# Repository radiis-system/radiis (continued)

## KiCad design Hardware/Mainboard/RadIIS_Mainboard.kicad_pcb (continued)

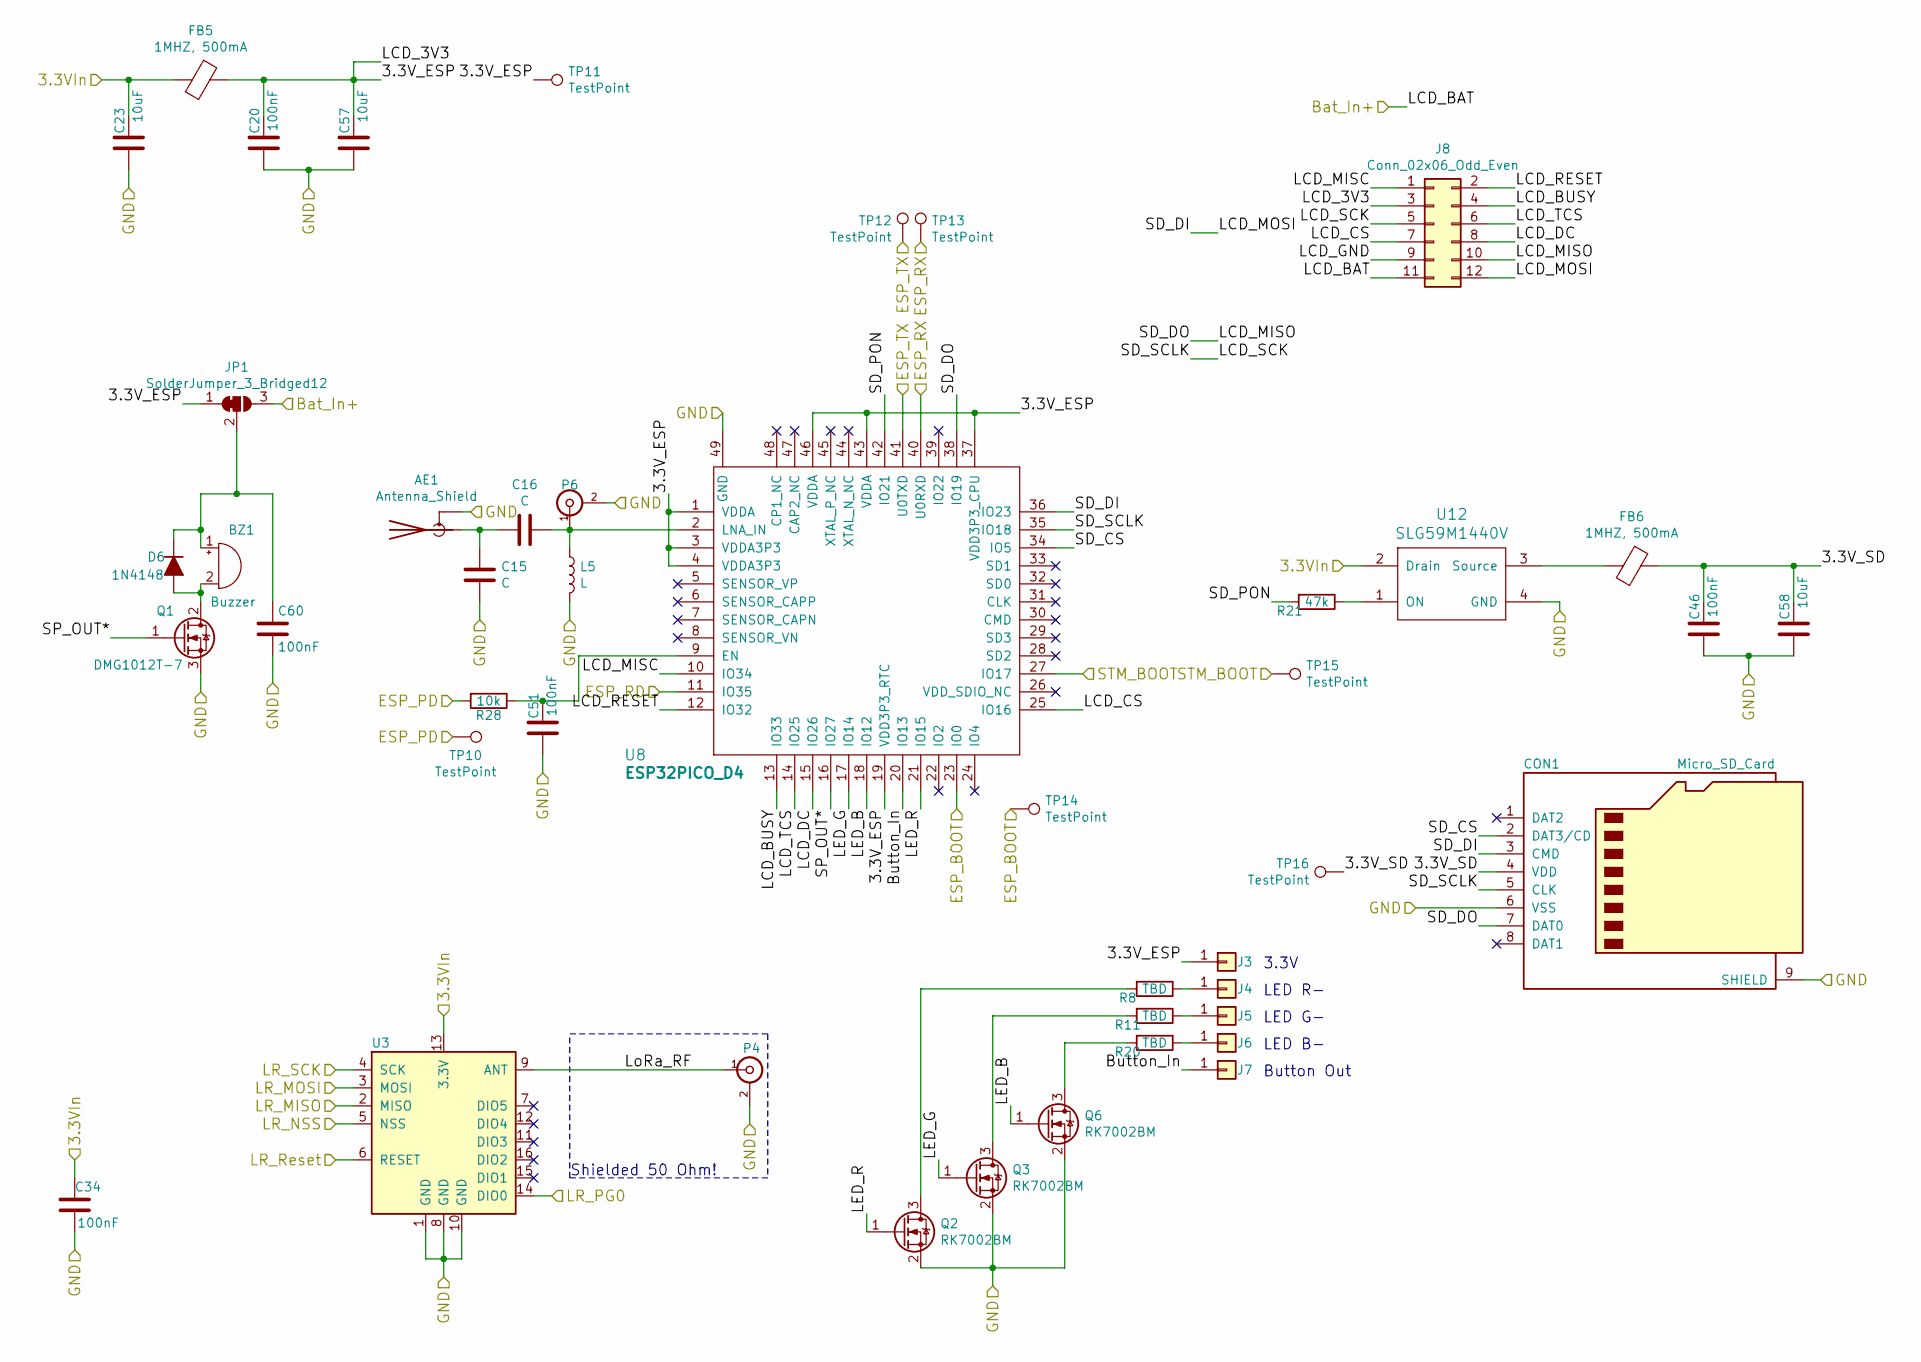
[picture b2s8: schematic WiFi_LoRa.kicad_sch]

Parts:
AE1: Antenna_Shield; Proant440; Digikey Nr 1532-1001-1-ND
BZ1: Buzzer; CUI_CMT-5023S-SMT; Digikey Nr 102-3743-1-ND
C15, C16: C; C_0402_1005Metric; Digikey Nr TBD (HF)
C20, C34, C46, C51, C60: 100nF; C_0603_1608Metric; Digikey Nr 1276-1000-1-ND
C23, C57, C58: 10uF; C_0603_1608Metric; Digikey Nr 478-10766-1-ND
CON1: Micro_SD_Card; microSD_HC_Wuerth_693072010801; Digikey Nr 732-3820-1-ND
D6: 1N4148; D_SOD-523; Digikey Nr 1N4148XTPMSCT-ND
FB5, FB6: 1MHZ, 500mA; L_0603_1608Metric; Digikey Nr 445-2205-1-ND
J3, J4, J5, J6, J7: Conn_01x01; 2108693-4; Digikey Nr A118885CT-ND
J8: Conn_02x06_Odd_Even; PinHeader_2x06_P1.27mm_Vertical_SMD; Digikey Nr S9012E-06-ND
JP1: SolderJumper_3_Bridged12; SolderJumper-3_P1.3mm_Bridged12_RoundedPad1.0x1.5mm; Digikey Nr NA
L5: L; L_0402_1005Metric; Digikey Nr TBD (HF)
P4, P6: A-1JB (U.FL); U.FL_SMD_Amp; Digikey Nr ARF1579CT-ND
Q1: DMG1012T-7; TSOT-23; Digikey Nr DMG1012T-7DICT-ND
Q2, Q3, Q6: RK7002BM; SOT-23; Digikey Nr RK7002BMT116CT-ND
R8, R11, R20: TBD; R_0603_1608Metric; Digikey Nr TBD
R21: 47k; R_0603_1608Metric; Digikey Nr 311-47.0KHRCT-ND
R28: 10k; R_0603_1608Metric; Digikey Nr 311-10.0KHRCT-ND
TP10, TP11, TP12, TP13, TP14, TP15, TP16: TestPoint; TestPoint_Pad_D1.5mm
U3: RFM95W-868S2; HOPERF_RFM9XW_SMD
U8: ESP32PICO_D4; QFN-48-1EP_7x7mm_Pitch0.5mm; Digikey Nr 1904-1029-1-ND
U12: SLG59M1440V; STDFN-4; Digikey Nr 1827-1058-1-ND

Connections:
+3V3: C23.2, C34.2, FB5.2, U3.13 (3.3V), U12.2 (Drain); also elsewhere on the board
+BATT: J8.11, JP1.3 (B); also elsewhere on the board
/Nucleo/STM_BOOT: TP15.1, U8.27 (IO17); also elsewhere on the board
/WiFi_LoRa/3.3V_ESP: C20.2, C57.2, FB5.1, J3.1, J8.3, JP1.1 (A), TP11.1, U8.1 (VDDA), U8.3 (VDDA3P3), U8.4 (VDDA3P3), U8.19 (VDD3P3_RTC), U8.37 (VDD3P3_CPU), U8.43 (VDDA), U8.46 (VDDA)
/WiFi_LoRa/3.3V_SD: C46.2, C58.2, CON1.4 (VDD), FB6.1, TP16.1
/WiFi_LoRa/Button_In: J7.1, U8.20 (IO13)
/WiFi_LoRa/ESP_BOOT: TP14.1, U8.23 (IO0); also elsewhere on the board
/WiFi_LoRa/ESP_PD: R28.2, TP10.1; also elsewhere on the board
/WiFi_LoRa/ESP_RD: U8.11 (IO35); also elsewhere on the board
/WiFi_LoRa/ESP_RX: TP13.1, U8.40 (U0RXD); also elsewhere on the board
/WiFi_LoRa/ESP_TX: TP12.1, U8.41 (U0TXD); also elsewhere on the board
/WiFi_LoRa/LCD_BUSY: J8.4, U8.13 (IO33)
/WiFi_LoRa/LCD_CS: J8.7, U8.25 (IO16)
/WiFi_LoRa/LCD_DC: J8.8, U8.15 (IO26)
/WiFi_LoRa/LCD_GND: J8.9
/WiFi_LoRa/LCD_MISC: J8.1, U8.10 (IO34)
/WiFi_LoRa/LCD_MISO: CON1.7 (DAT0), J8.10, U8.38 (IO19)
/WiFi_LoRa/LCD_MOSI: CON1.3 (CMD), J8.12, U8.36 (IO23)
/WiFi_LoRa/LCD_RESET: J8.2, U8.12 (IO32)
/WiFi_LoRa/LCD_SCK: CON1.5 (CLK), J8.5, U8.35 (IO18)
/WiFi_LoRa/LCD_TCS: J8.6, U8.14 (IO25)
/WiFi_LoRa/LED_B: Q6.1 (G), U8.18 (IO12)
/WiFi_LoRa/LED_G: Q3.1 (G), U8.17 (IO14)
/WiFi_LoRa/LED_R: Q2.1 (G), U8.21 (IO15)
/WiFi_LoRa/LR_MISO: U3.2 (MISO); also elsewhere on the board
/WiFi_LoRa/LR_MOSI: U3.3 (MOSI); also elsewhere on the board
/WiFi_LoRa/LR_NSS: U3.5 (NSS); also elsewhere on the board
/WiFi_LoRa/LR_PG0: U3.14 (DIO0); also elsewhere on the board
/WiFi_LoRa/LR_Reset: U3.6 (RESET); also elsewhere on the board
/WiFi_LoRa/LR_SCK: U3.4 (SCK); also elsewhere on the board
/WiFi_LoRa/LoRa_RF: P4.1 (In), U3.9 (ANT)
/WiFi_LoRa/SD_CS: CON1.2 (DAT3/CD), U8.34 (IO5)
/WiFi_LoRa/SD_PON: R21.2, U8.42 (IO21)
/WiFi_LoRa/SP_OUT*: Q1.1 (G), U8.16 (IO27)
GND: AE1.2 (Shield), C15.1, C20.1, C23.1, C34.1, C46.1, C51.1, C57.1, C58.1, C60.2, CON1.6 (VSS), CON1.9 (SHIELD), L5.2, P4.2 (Ext), P6.2 (Ext), Q1.3 (S), Q2.2 (S), Q3.2 (S), Q6.2 (S), U3.1 (GND), U3.8 (GND), U3.10 (GND), U8.49 (GND), U12.4 (GND); also elsewhere on the board
unnamed: AE1.1 (A), C15.2, C16.2
unnamed: BZ1.1 (-), C60.1, D6.1 (K), JP1.2 (C)
unnamed: BZ1.2 (+), D6.2 (A), Q1.2 (D)
unnamed: C16.1, L5.1, P6.1 (In), U8.2 (LNA_IN)
unnamed: C51.2, R28.1, U8.9 (EN)
unnamed: FB6.2, U12.3 (Source)
unnamed: J4.1, R8.1
unnamed: J5.1, R11.1
unnamed: J6.1, R20.1
unnamed: Q2.3 (D), R8.2
unnamed: Q3.3 (D), R11.2
unnamed: Q6.3 (D), R20.2
unnamed: R21.1, U12.1 (ON)

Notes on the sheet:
LED B-
Shielded 50 Ohm!
3.3V
Button Out
LED G-
LED R-

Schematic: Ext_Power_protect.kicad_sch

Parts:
C39: 100nF 50V; C_0603_1608Metric; Digikey Nr 1292-1392-1-ND
C40: 10uF 50V; C_1206_3216Metric; Digikey Nr 1276-6736-1-ND
C41: 22nF; C_0603_1608Metric; Digikey Nr 399-1280-1-ND
C42, C43: 22uF; C_0805_2012Metric; Digikey Nr 1276-6780-1-ND
D7: D_Schottky_ALT; D_SOD-123F; Digikey Nr MBR230LSFT1GOSCT-ND
FB2: 1MHZ, 500mA; L_0603_1608Metric; Digikey Nr 445-2205-1-ND
L2: 4.7uH; L_Taiyo-Yuden_NR-50xx; Digikey Nr 587-2407-1-ND
R31: NA/0; R_0603_1608Metric; Digikey Nr 311-0.0GRCT-ND
R32: 10k; R_0603_1608Metric; Digikey Nr 311-10.0KHRCT-ND
R33: 47k; R_0603_1608Metric; Digikey Nr 311-47.0KHRCT-ND
U13: TS30041/11; QFN-16-1EP_3x3mm_Pitch0.5mm; Digikey Nr TS30041-M000QFNRCT-ND
W20: TEST_1P; TestPoint_Pad_D1.0mm; Digikey Nr NA

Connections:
/Ext_Power_protect/EN_DCDCin: U13.9 (EN); also elsewhere on the board
/Ext_Power_protect/PG_DCDCin: U13.8 (PG); also elsewhere on the board
/Ext_Power_protect/VSW: C41.2, D7.1 (K), L2.1, U13.1 (VSW), U13.12 (VSW), U13.13 (VSW), U13.16 (VSW)
/Ext_Vin: FB2.2; also elsewhere on the board
/Reg_5V: C42.2, C43.2, L2.2, R31.1, R33.1, W20.1; also elsewhere on the board
GND: C39.1, C40.2, C42.1, C43.1, D7.2 (A), R32.1, U13.4 (GND), U13.14 (PGND), U13.15 (PGND), U13.17 (GND); also elsewhere on the board
unnamed: C39.2, C40.1, FB2.1, R31.2, U13.2 (VCC), U13.3 (VCC), U13.11 (VCC)
unnamed: C41.1, U13.10 (BST)
unnamed: R32.2, R33.2, U13.5 (FB)
unnamed: U13.6 (NC), U13.7 (NC)

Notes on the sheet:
If TS300x1 not assembled, R = 0 Ohm
max 40V
shielded

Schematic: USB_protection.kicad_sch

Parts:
C49: 680nF; C_0603_1608Metric; Digikey Nr 732-7970-1-ND
FB3, FB4: Ferrite Bead; L_0603_1608Metric; Digikey Nr 732-1593-1-ND
R35, R36: 22; R_0603_1608Metric; Digikey Nr 311-22.0HRCT-ND
U14: IP4220CZ6; SC-74; Digikey Nr 1727-3578-1-ND
W21: TEST_1P; TestPoint_Pad_D1.0mm; Digikey Nr NA

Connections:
+5VP: FB3.2, W21.1; also elsewhere on the board
/USB_Protection/Din+: R36.1, U14.1 (IO1); also elsewhere on the board
/USB_Protection/Din-: R35.1, U14.3 (IO2); also elsewhere on the board
/USB_Protection/Dout+: R36.2; also elsewhere on the board
/USB_Protection/Dout-: R35.2; also elsewhere on the board
/USB_Protection/ID_In: U14.4 (IO3); also elsewhere on the board
/USB_Protection/VBus_In: FB4.1, U14.5 (Vp); also elsewhere on the board
GND: C49.1, U14.2 (GND); also elsewhere on the board
unnamed: C49.2, FB3.1, FB4.2

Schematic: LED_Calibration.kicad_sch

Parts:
D5: LED; LED_0603_1608Metric; Digikey Nr 492-1949-1-ND
R38: 1k; R_0603_1608Metric; Digikey Nr 311-1.00KHRCT-ND
TP23: TestPoint; TestPoint_Pad_D1.5mm

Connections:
/Nucleo/LED_Trigger(PA8)*: R38.2; also elsewhere on the board
GND: D5.1 (K); also elsewhere on the board
unnamed: D5.2 (A), R38.1, TP23.1

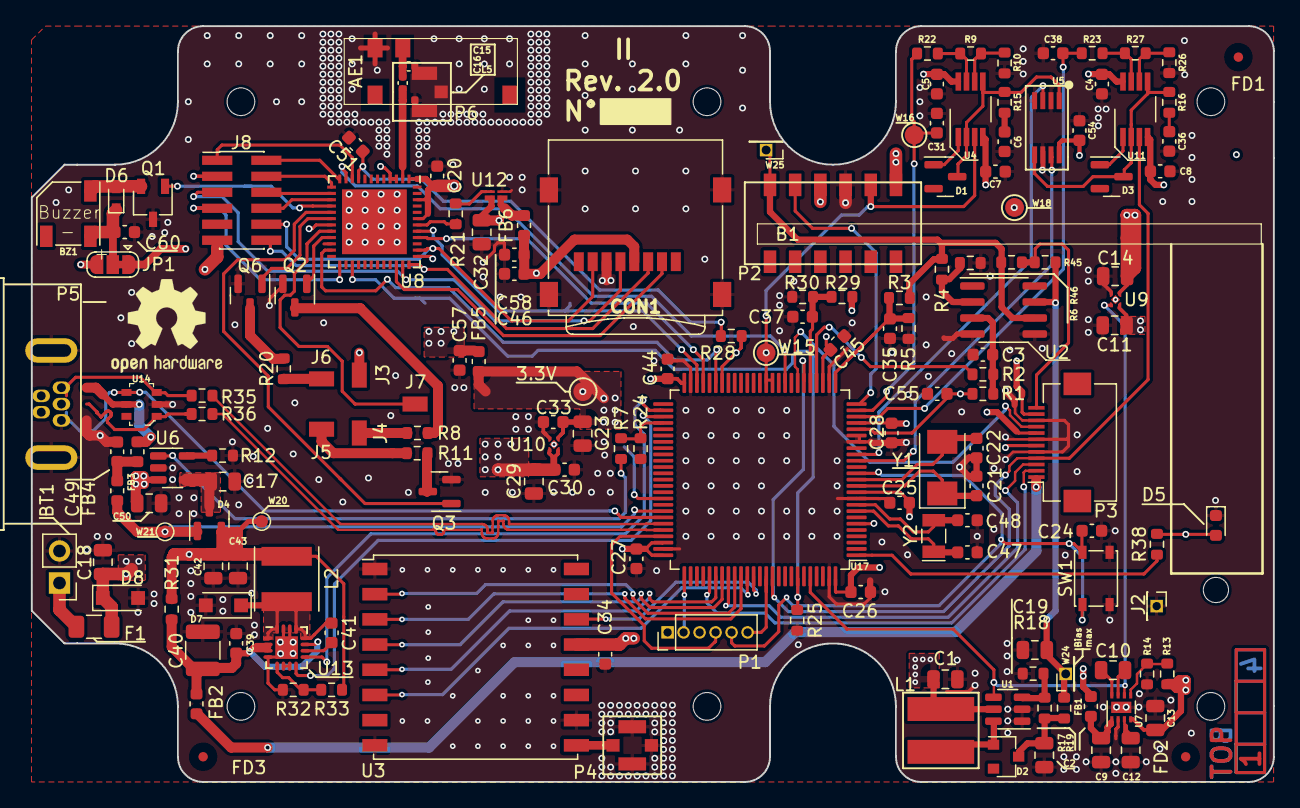
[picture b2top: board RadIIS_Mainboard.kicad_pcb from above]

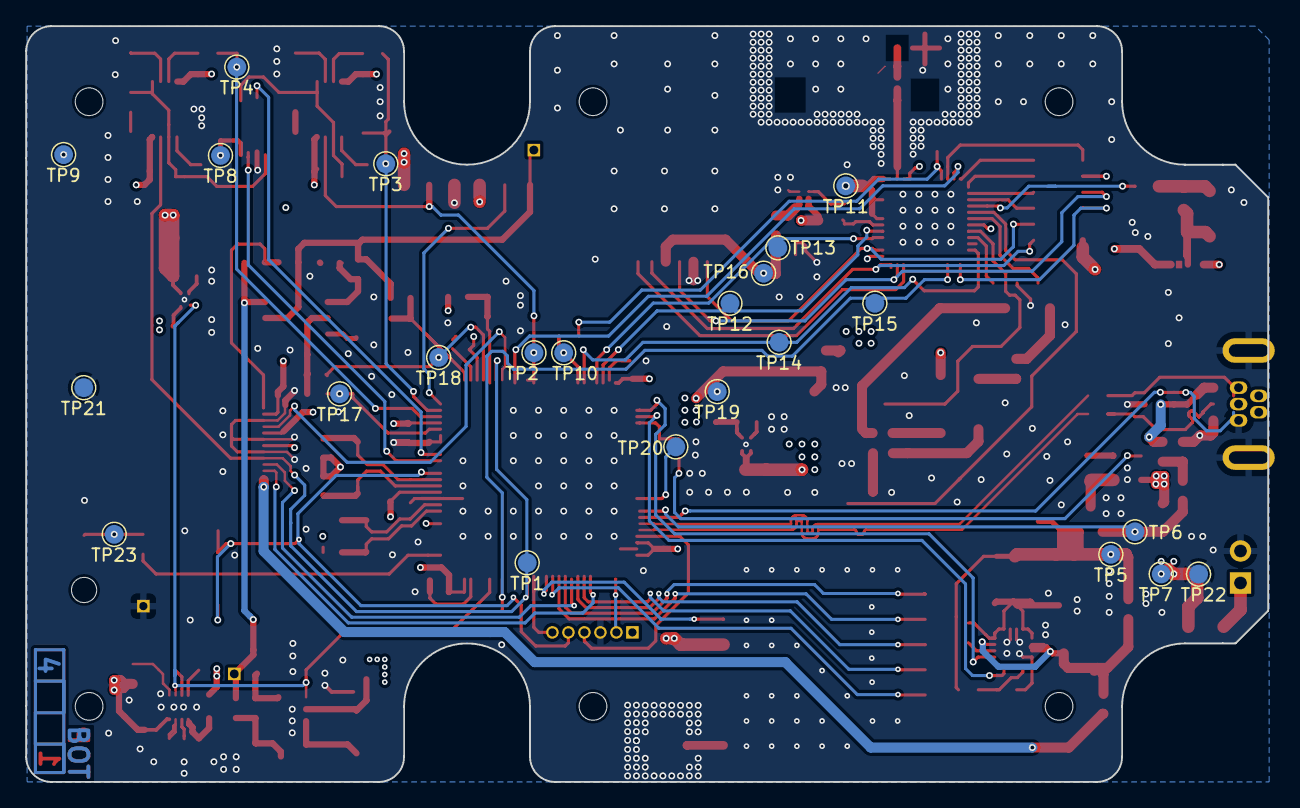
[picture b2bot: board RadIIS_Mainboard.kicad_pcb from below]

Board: 4 copper layers, 98.6 x 60.0 mm, 187 parts (23 on the bottom side), 120 nets.

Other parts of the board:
FD1, FD2, FD3: Fiducial_0.75mm_Mask2.25mm

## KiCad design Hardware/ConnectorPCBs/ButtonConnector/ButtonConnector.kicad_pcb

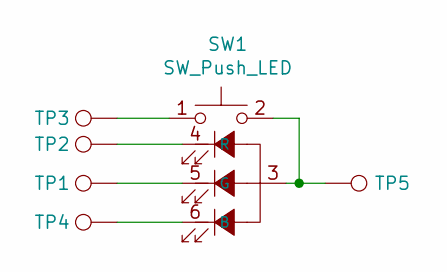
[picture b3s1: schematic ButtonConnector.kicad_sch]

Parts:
SW1: SW_Push_LED; MBP16_RGB_PCB
TP1, TP2, TP3, TP4, TP5: Pad; TestPoint_Pad_2.0x2.0mm

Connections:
unnamed: SW1.1, TP3.1
unnamed: SW1.2, SW1.3, TP5.1
unnamed: SW1.4 (R), TP2.1
unnamed: SW1.5 (G), TP1.1
unnamed: SW1.6 (B), TP4.1

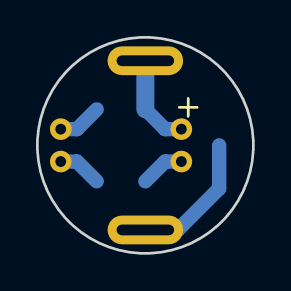
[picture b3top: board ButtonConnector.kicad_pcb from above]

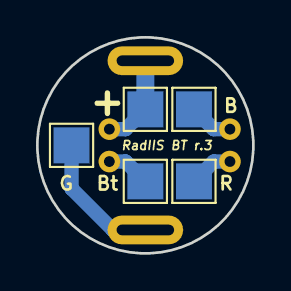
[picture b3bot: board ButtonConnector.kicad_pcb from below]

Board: 2 copper layers, 12.0 x 12.0 mm, 6 parts (5 on the bottom side), 5 nets.

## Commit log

2024-10-31 Init fresh git as public RadIIS space
2024-10-31 [git] Added git config files
2024-10-31 [Hardware] Added mainboard and module files
2024-10-31 [git] Ignore 3D files for now
2024-10-31 [doc] Added Sphinx doc files
2024-10-31 [doc] Added software doc file
2024-10-31 [doc] Added pictures for the ReadMe
2024-10-31 [doc] Update README.md
2024-10-31 [git] Create LICENSE CERN-OHL-S
